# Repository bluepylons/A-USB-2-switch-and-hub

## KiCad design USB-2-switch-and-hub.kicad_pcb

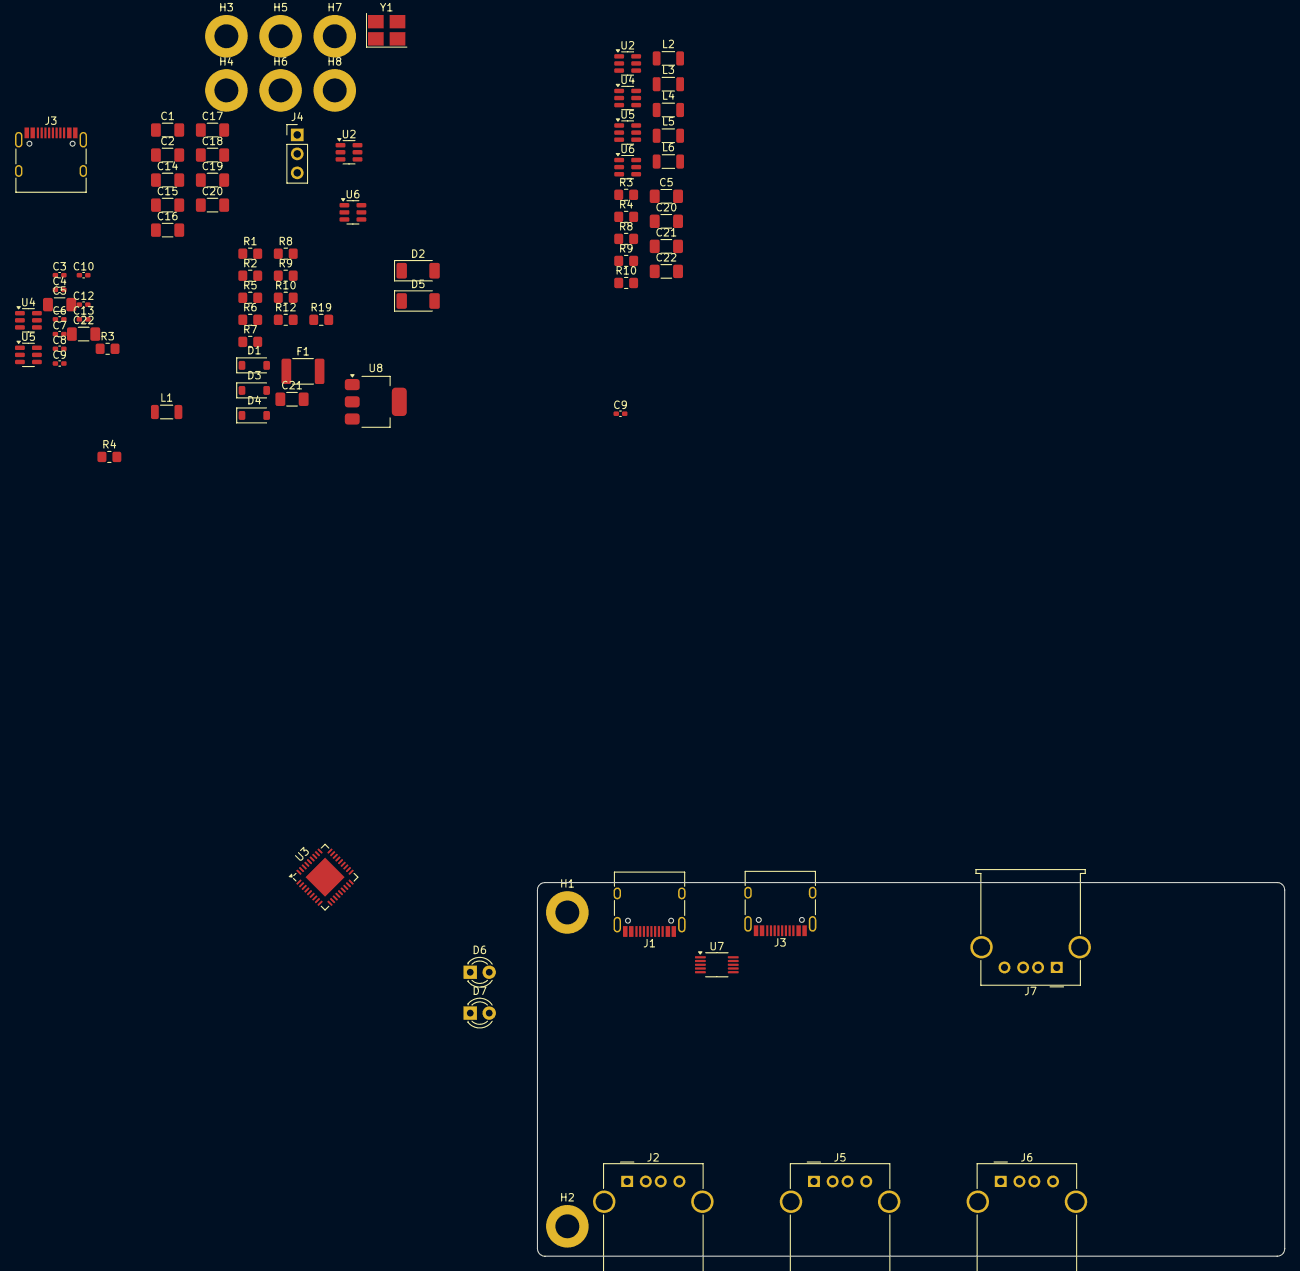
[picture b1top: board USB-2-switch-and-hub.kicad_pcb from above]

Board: 4 copper layers, 100.0 x 50.0 mm, 85 parts (0 on the bottom side), 47 nets, no tracks yet.

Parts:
C1, C2, C5, C5#2, C14, C15, C16, C17, C18, C19, C20, C20#2, C21, C21#2, C22, C22#2: 10uF; C_1206_3216Metric_Pad1.33x1.80mm_HandSolder
C3, C4: 18pF; C_0402_1005Metric_Pad0.74x0.62mm_HandSolder
C6, C7, C8, C9, C9#2, C10, C12, C13: 100nF; C_0402_1005Metric_Pad0.74x0.62mm_HandSolder
D1: SMF9.0CA; D_SOD-123
D2, D5: D_Schottky; D_SOD-128
D3, D4: RB060M-60TR; D_SOD-123
D6, D7: LED; LED_D3.0mm_Clear
F1: 1812L075PR; Fuse_1812_4532Metric_Pad1.30x3.40mm_HandSolder
H1, H2, H3, H4, H5, H6, H7, H8: MountingHole_Pad; MountingHole_3.2mm_M3_ISO7380_Pad
J1, J3, J3#2: USB_C_Receptacle_USB2.0; USB_C_Receptacle_HRO_TYPE-C-31-M-12
J2, J5, J6, J7: USB_A; USB_A_Molex_67643_Horizontal
J4: Conn_01x03; PinHeader_1x03_P2.54mm_Vertical
L1, L2, L3, L4, L5, L6: 60R@100MHz; L_1206_3216Metric
R1, R2, R3, R3#2, R4, R4#2: 5.1k; R_0805_2012Metric_Pad1.20x1.40mm_HandSolder
R5, R8, R8#2, R9, R9#2, R10, R10#2: 12k; R_0805_2012Metric_Pad1.20x1.40mm_HandSolder
R6, R7: 56k; R_0805_2012Metric_Pad1.20x1.40mm_HandSolder
R12: 100k; R_0805_2012Metric_Pad1.20x1.40mm_HandSolder
R19: 1M; R_0805_2012Metric_Pad1.20x1.40mm_HandSolder
U2, U2#2, U4, U4#2, U5, U5#2, U6, U6#2: USBLC6-2SC6; SOT-23-6
U3: USB2514B_Bi; QFN-36-1EP_6x6mm_P0.5mm_EP3.7x3.7mm
U7: TS3USB30EDGSR; VSSOP-10_3x3mm_P0.5mm
U8: TLV1117-33; SOT-223-3_TabPin2
Y1: 24MHz; Crystal_SMD_3225-4Pin_3.2x2.5mm_HandSoldering

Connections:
+3V3: C1.1, C2.1, C5.1, C5#2.1, C6.1, C7.1, C8.1, C9.1, C9#2.1, C10.1, C12.1, C13.1, C15.1, C16.1, C17.1, D4.2 (A), J4.1, R10.2, R10#2.2, U3.5 (VDDA33), U3.10 (VDDA33), U3.15 (VDD33), U3.23 (VDD33), U3.26 (RESET_N), U3.27 (VBUS_DET), U3.29 (VDDA33), U3.36 (VDDA33), U7.10 (VCC), U8.2 (VO)
+5V: C14.1, C18.1, C19.1, C20.1, C20#2.1, C21.1, C21#2.1, C22.1, C22#2.1, D1.2 (A2), D3.1 (K), D4.1 (K), F1.2, J2.1 (VBUS), J5.1 (VBUS), J6.1 (VBUS), J7.1 (VBUS), R12.2, U2.5 (VBUS), U2#2.5 (VBUS), U4.5 (VBUS), U4#2.5 (VBUS), U5.5 (VBUS), U5#2.5 (VBUS), U6.5 (VBUS), U6#2.5 (VBUS), U8.3 (VI)
D1+: U2.6 (I/O1), U2#2.6 (I/O1), U3.2 (USBDP_DN1/PRT_DIS_P1)
D1-: U2.4 (I/O2), U2#2.4 (I/O2), U3.1 (USBDM_DN1/PRT_DIS_M1)
D2+: U3.4 (USBDP_DN2/PRT_DIS_P2), U4.6 (I/O1), U4#2.6 (I/O1)
D2-: U3.3 (USBDM_DN2/PRT_DIS_M2), U4.4 (I/O2), U4#2.4 (I/O2)
D3+: U3.7 (USBDP_DN3/PRT_DIS_P3), U5.6 (I/O1), U5#2.6 (I/O1)
D3-: U3.6 (USBDM_DN3/PRT_DIS_M3), U5.4 (I/O2), U5#2.4 (I/O2)
D4+: U3.9 (USBDP_DN4/PRT_DIS_P4), U6.6 (I/O1), U6#2.6 (I/O1)
D4-: U3.8 (USBDM_DN4/PRT_DIS_M4), U6.4 (I/O2), U6#2.4 (I/O2)
DUP1+: J1.A6 (D+), J1.B6 (D+), U7.2 (D1+)
DUP1-: J1.A7 (D-), J1.B7 (D-), U7.8 (D1-)
DUP2+: J3.A6 (D+), J3.B6 (D+), J3#2.A6 (D+), J3#2.B6 (D+), U7.3 (D2+)
DUP2-: J3.A7 (D-), J3.B7 (D-), J3#2.A7 (D-), J3#2.B7 (D-), U7.7 (D2-)
DUP+: U3.31 (USBDP_UP), U7.4 (D+)
DUP-: U3.30 (USBDM_UP), U7.6 (D-)
GND: C1.2, C2.2, C3.1, C4.1, C5.2, C5#2.2, C6.2, C7.2, C8.2, C9.2, C9#2.2, C10.2, C12.2, C13.2, C14.2, C15.2, C16.2, C17.2, C18.2, C19.2, C20.2, C20#2.2, C21.2, C21#2.2, C22.2, C22#2.2, D3.2 (A), D6.1 (K), J1.A1 (GND), J1.A12 (GND), J1.B1 (GND), J1.B12 (GND), J2.5 (Shield), J3.A1 (GND), J3.A12 (GND), J3.B1 (GND), J3.B12 (GND), J3#2.A1 (GND), J3#2.A12 (GND), J3#2.B1 (GND), J3#2.B12 (GND), J4.3, J5.5 (Shield), J6.5 (Shield), J7.5 (Shield), L1.1, L2.2, L3.1, L4.2, L5.2, L6.2, R1.2, R2.2, R3.2, R3#2.2, R4.2, R4#2.2, R5.1, R6.1, R7.1, R8.1, R8#2.1, R12.1, U2.2 (GND), U2#2.2 (GND), U3.37 (VSS), U4.2 (GND), U4#2.2 (GND), U5.2 (GND), U5#2.2 (GND), U6.2 (GND), U6#2.2 (GND), U7.5 (GND), U7.9 (~OE), U8.1 (GND), Y1.2, Y1.4
GNDPWR: D1.1 (A1), H1.1, H2.1, H3.1, H4.1, H5.1, H6.1, H7.1, H8.1
unnamed: D2.2 (A), J1.A4 (VBUS), J1.A9 (VBUS), J1.B4 (VBUS), J1.B9 (VBUS)
unnamed: D5.2 (A), J3.A4 (VBUS), J3.A9 (VBUS), J3.B4 (VBUS), J3.B9 (VBUS), J3#2.A4 (VBUS), J3#2.A9 (VBUS), J3#2.B4 (VBUS), J3#2.B9 (VBUS)
unnamed: D6.2 (A), R9.1, R9#2.1
unnamed: D7.2 (A), R10.1, R10#2.1
unnamed: J1.A5 (CC1), R1.1
unnamed: J1.B5 (CC2), R2.1
unnamed: J1.S1 (SHIELD), L1.2
unnamed: J2.3 (D+), U2.1 (I/O1), U2#2.1 (I/O1)
unnamed: J2.2 (D-), U2.3 (I/O2), U2#2.3 (I/O2)
unnamed: J2.4 (GND), L2.1
unnamed: J3.A5 (CC1), J3#2.A5 (CC1), R3.1, R3#2.1
unnamed: J3.B5 (CC2), J3#2.B5 (CC2), R4.1, R4#2.1
unnamed: J3.S1 (SHIELD), J3#2.S1 (SHIELD), L3.2
unnamed: J5.3 (D+), U4.1 (I/O1), U4#2.1 (I/O1)
unnamed: J5.2 (D-), U4.3 (I/O2), U4#2.3 (I/O2)
unnamed: J5.4 (GND), L4.1
unnamed: J6.3 (D+), U5.1 (I/O1), U5#2.1 (I/O1)
unnamed: J6.2 (D-), U5.3 (I/O2), U5#2.3 (I/O2)
unnamed: J6.4 (GND), L5.1
unnamed: J7.3 (D+), U6.1 (I/O1), U6#2.1 (I/O1)
unnamed: J7.2 (D-), U6.3 (I/O2), U6#2.3 (I/O2)
unnamed: J7.4 (GND), L6.1
unnamed: R7.2, U3.25 (HS_IND/CFG_SEL1)
unnamed: R5.2, U3.35 (RBIAS)
unnamed: R6.2, U3.28 (SUSP_IND/LOCAL_PWR/NON_REM0)
unnamed: C3.2, R19.1, U3.33 (XTALIN/CLKIN), Y1.1
unnamed: C4.2, R19.2, U3.32 (XTALOUT), Y1.3
SELECT: D7.1 (K), J4.2, R8.2, R8#2.2, R9.2, R9#2.2, U7.1 (S)
VBUS: D2.1 (K), D5.1 (K), F1.1

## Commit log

2025-04-05 WIP initial release
2025-04-05 Assigned footprints
2025-04-16 Some work
    Probably won't get prototyped anytime soon though
